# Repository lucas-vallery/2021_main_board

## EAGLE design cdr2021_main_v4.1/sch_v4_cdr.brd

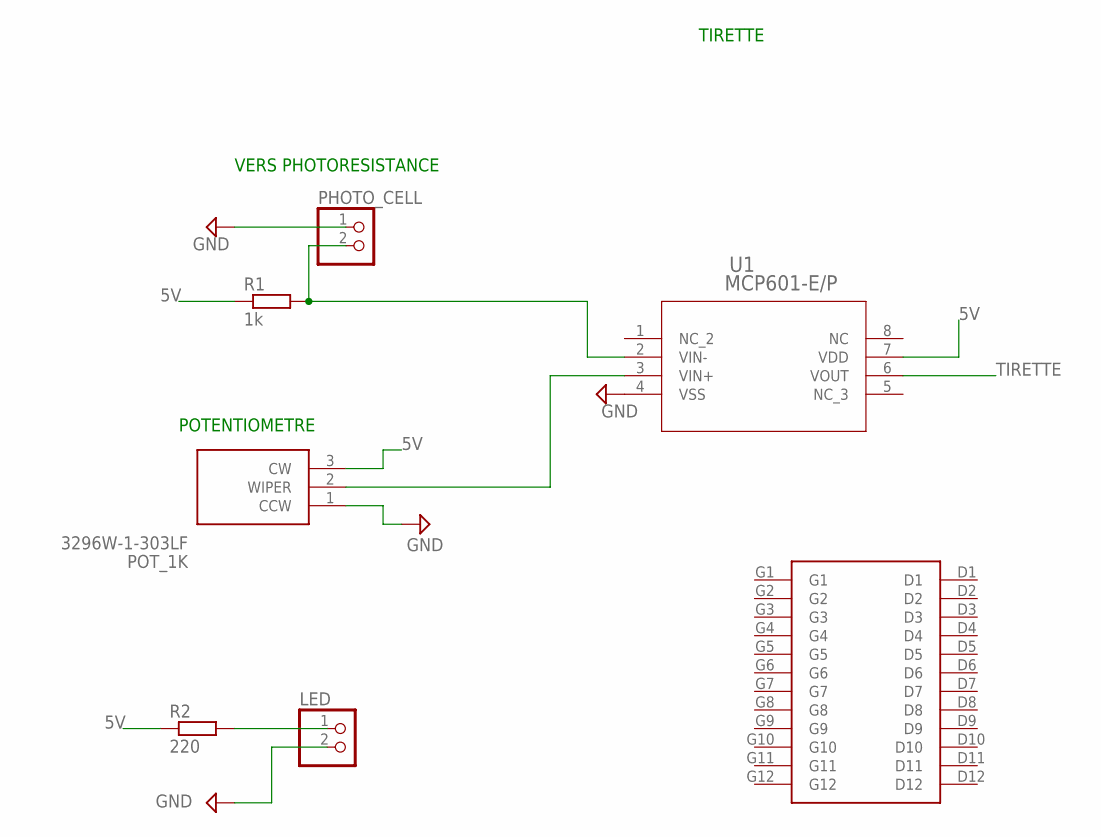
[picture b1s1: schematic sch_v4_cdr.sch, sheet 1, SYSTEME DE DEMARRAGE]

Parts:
LED: PINHD-1X2; 1X02
PHOTO_CELL: PINHD-1X2; 1X02
POT_1K: 3296W-1-303LF; 3296W-1
R1: 1k; 0204/7
R2: 220; 0204/7
U1: MCP601-E/P; PDIP8_300MC_MCH
U$5: MATRIX_12X12

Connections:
5V: POT_1K.3 (CW), R1.1, R2.1, U1.7 (VDD); also elsewhere on the board
GND: LED.2, PHOTO_CELL.1, POT_1K.1 (CCW), U1.4 (VSS); also elsewhere on the board
unnamed: PHOTO_CELL.2, R1.2, U1.2 (VIN-)
unnamed: POT_1K.2 (WIPER), U1.3 (VIN+)
unnamed: LED.1, R2.2
TIRETTE: U1.6 (VOUT); also elsewhere on the board

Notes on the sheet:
VERS PHOTORESISTANCE
POTENTIOMETRE
TIRETTE

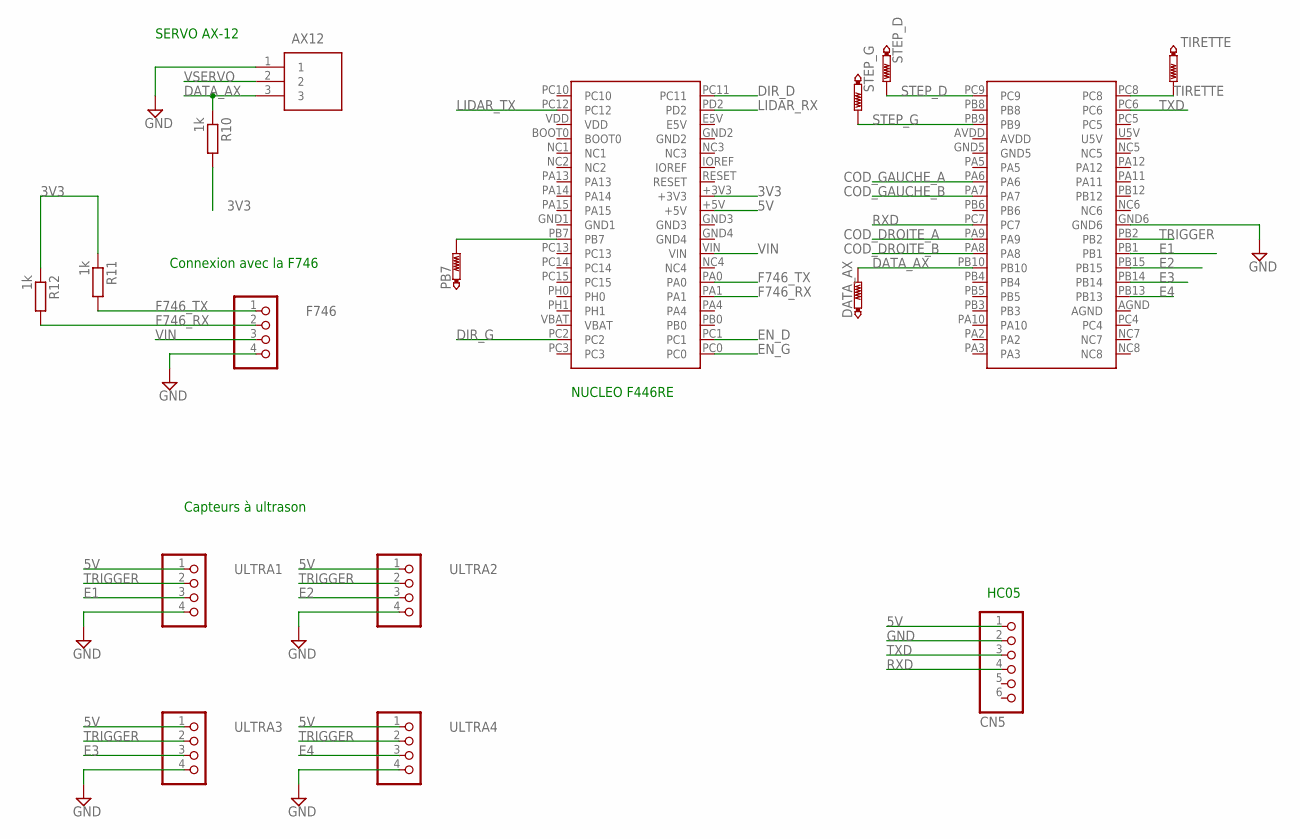
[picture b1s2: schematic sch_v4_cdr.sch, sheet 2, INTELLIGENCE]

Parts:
AX12: 22-03-5035; SHDR3W60P0X250_1X3_990X490X590
DATA_AX: PTR1PAD1-13; P1-13
F746: PINHD-1X4; 1X04
JP4: CN5; 1X06
PB7: PTR1PAD1-13; P1-13
R10, R11, R12: 1k; 0204/7
STEP_D: PTR1PAD1-13; P1-13
STEP_G: PTR1PAD1-13; P1-13
TIRETTE: PTR1PAD1-13; P1-13
U$1: NUCLEO_F446RE; MB1136
ULTRA1, ULTRA2, ULTRA3, ULTRA4: PINHD-1X4; 1X04

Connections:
3V3: R10.2, R11.1, R12.1, U$1.+3V3
5V: JP4.1, U$1.+5V, ULTRA1.1, ULTRA2.1, ULTRA3.1, ULTRA4.1; also elsewhere on the board
COD_DROITE_A: U$1.PA9; also elsewhere on the board
COD_DROITE_B: U$1.PA8; also elsewhere on the board
COD_GAUCHE_A: U$1.PA6; also elsewhere on the board
COD_GAUCHE_B: U$1.PA7; also elsewhere on the board
DATA_AX: AX12.3, DATA_AX.TP, R10.1, U$1.PB10
DIR_D: U$1.PC11; also elsewhere on the board
DIR_G: U$1.PC2; also elsewhere on the board
E1: U$1.PB1, ULTRA1.3
E2: U$1.PB15, ULTRA2.3
E3: U$1.PB14, ULTRA3.3
E4: U$1.PB13, ULTRA4.3
EN_D: U$1.PC1; also elsewhere on the board
EN_G: U$1.PC0; also elsewhere on the board
F746_RX: F746.2, R12.2, U$1.PA1
F746_TX: F746.1, R11.2, U$1.PA0
GND: AX12.1, F746.4, JP4.2, U$1.GND6, ULTRA1.4, ULTRA2.4, ULTRA3.4, ULTRA4.4; also elsewhere on the board
LIDAR_RX: U$1.PD2; also elsewhere on the board
LIDAR_TX: U$1.PC12; also elsewhere on the board
unnamed: PB7.TP, U$1.PB7
RXD: JP4.4, U$1.PC7
STEP_D: STEP_D.TP, U$1.PC9; also elsewhere on the board
STEP_G: STEP_G.TP, U$1.PB9; also elsewhere on the board
TIRETTE: TIRETTE.TP, U$1.PC8; also elsewhere on the board
TRIGGER: U$1.PB2, ULTRA1.2, ULTRA2.2, ULTRA3.2, ULTRA4.2
TXD: JP4.3, U$1.PC6
VIN: F746.3, U$1.VIN; also elsewhere on the board
VSERVO: AX12.2; also elsewhere on the board

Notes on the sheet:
NUCLEO F446RE
Connexion avec la F746
SERVO AX-12
Capteurs à ultrason
HC05

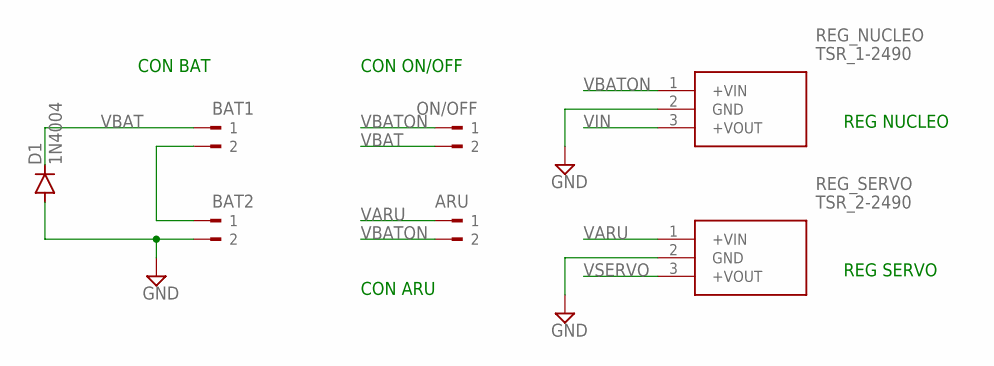
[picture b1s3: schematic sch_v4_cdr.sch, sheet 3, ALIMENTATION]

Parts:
ARU: 180G-2
BAT1, BAT2: 180G-2
D1: 1N4004; DO41-10
ON/OFF: 180G-2
REG_NUCLEO: TSR_1-2490; TSR_1-24XX
REG_SERVO: TSR_2-2490; TSR_2-24XX

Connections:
GND: BAT2.2, D1.A, REG_NUCLEO.2 (GND), REG_SERVO.2 (GND); also elsewhere on the board
unnamed: BAT1.2, BAT2.1
VARU: ARU.1, REG_SERVO.1 (+VIN); also elsewhere on the board
VBAT: BAT1.1, D1.C, ON/OFF.2
VBATON: ARU.2, ON/OFF.1, REG_NUCLEO.1 (+VIN)
VIN: REG_NUCLEO.3 (+VOUT); also elsewhere on the board
VSERVO: REG_SERVO.3 (+VOUT); also elsewhere on the board

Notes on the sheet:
CON BAT
CON ON/OFF
CON ARU
REG NUCLEO
REG SERVO

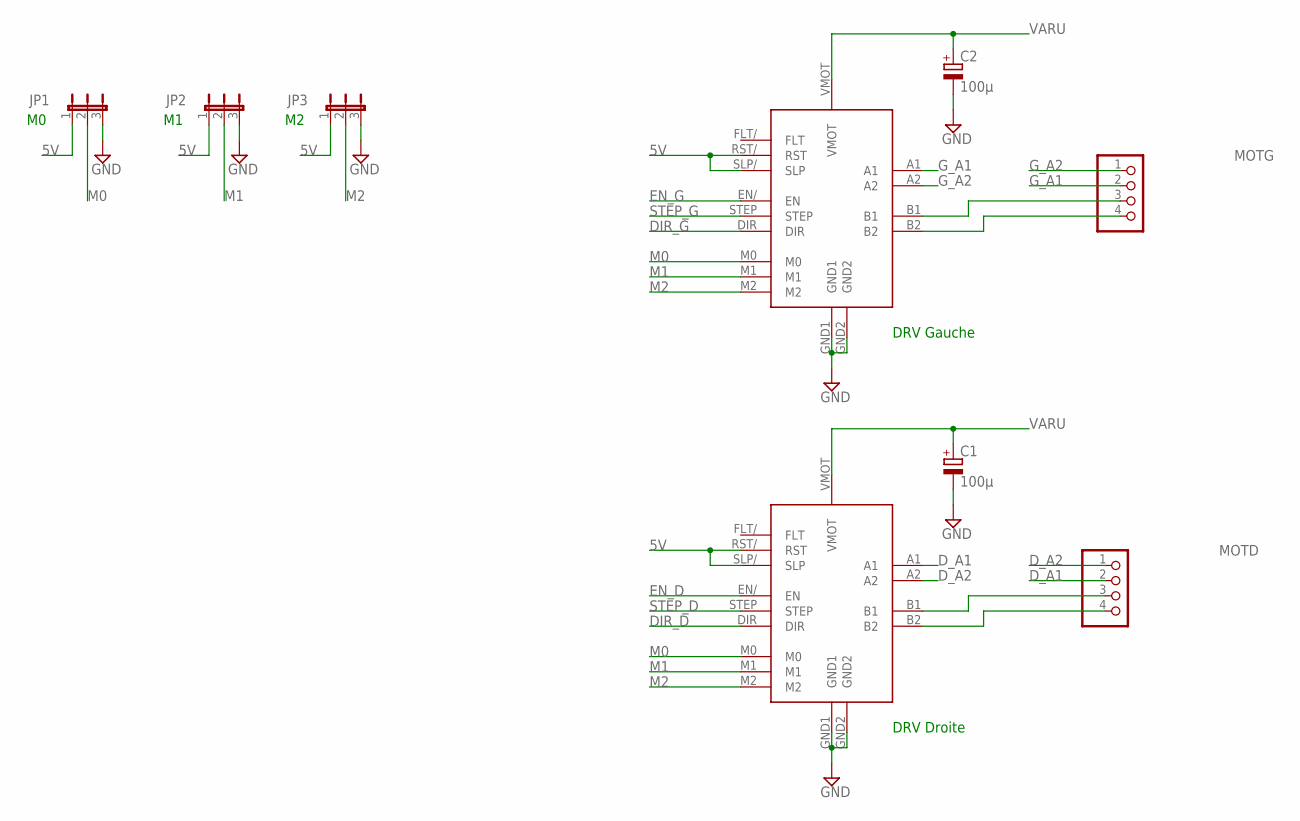
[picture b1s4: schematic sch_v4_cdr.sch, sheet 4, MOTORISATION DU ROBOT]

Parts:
C1, C2: 100µ; SANYO-OSCON_A
JP1, JP2, JP3: JP2E; JP2
MOTD: PINHD-1X4; 1X04
MOTG: PINHD-1X4; 1X04
U$2, U$3: POLOLU_DRV8825

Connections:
5V: JP1.1, JP2.1, JP3.1, U$2.RST/ (RST), U$2.SLP/ (SLP), U$3.RST/ (RST), U$3.SLP/ (SLP); also elsewhere on the board
DIR_D: U$3.DIR; also elsewhere on the board
DIR_G: U$2.DIR; also elsewhere on the board
D_A1: MOTD.2, U$3.A1
D_A2: MOTD.1, U$3.A2
EN_D: U$3.EN/ (EN); also elsewhere on the board
EN_G: U$2.EN/ (EN); also elsewhere on the board
GND: C1.-, C2.-, JP1.3, JP2.3, JP3.3, U$2.GND1, U$2.GND2, U$3.GND1, U$3.GND2; also elsewhere on the board
G_A1: MOTG.2, U$2.A1
G_A2: MOTG.1, U$2.A2
M0: JP1.2, U$2.M0, U$3.M0
M1: JP2.2, U$2.M1, U$3.M1
M2: JP3.2, U$2.M2, U$3.M2
unnamed: MOTG.3, U$2.B1
unnamed: MOTG.4, U$2.B2
unnamed: MOTD.3, U$3.B1
unnamed: MOTD.4, U$3.B2
STEP_D: U$3.STEP; also elsewhere on the board
STEP_G: U$2.STEP; also elsewhere on the board
VARU: C1.+, C2.+, U$2.VMOT, U$3.VMOT; also elsewhere on the board

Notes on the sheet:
DRV Gauche
DRV Droite

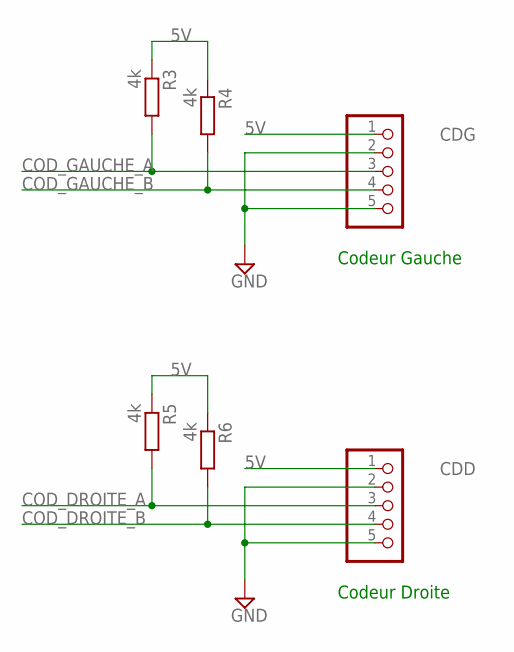
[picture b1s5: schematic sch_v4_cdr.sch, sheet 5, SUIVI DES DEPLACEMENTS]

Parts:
CDD: PINHD-1X5; 1X05
CDG: PINHD-1X5; 1X05
R3, R4, R5, R6: 4k; 0204/7

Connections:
5V: CDD.1, CDG.1, R3.1, R4.1, R5.1, R6.1; also elsewhere on the board
COD_DROITE_A: CDD.3, R5.2; also elsewhere on the board
COD_DROITE_B: CDD.4, R6.2; also elsewhere on the board
COD_GAUCHE_A: CDG.3, R3.2; also elsewhere on the board
COD_GAUCHE_B: CDG.4, R4.2; also elsewhere on the board
GND: CDD.2, CDD.5, CDG.2, CDG.5; also elsewhere on the board

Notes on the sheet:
Codeur Gauche
Codeur Droite

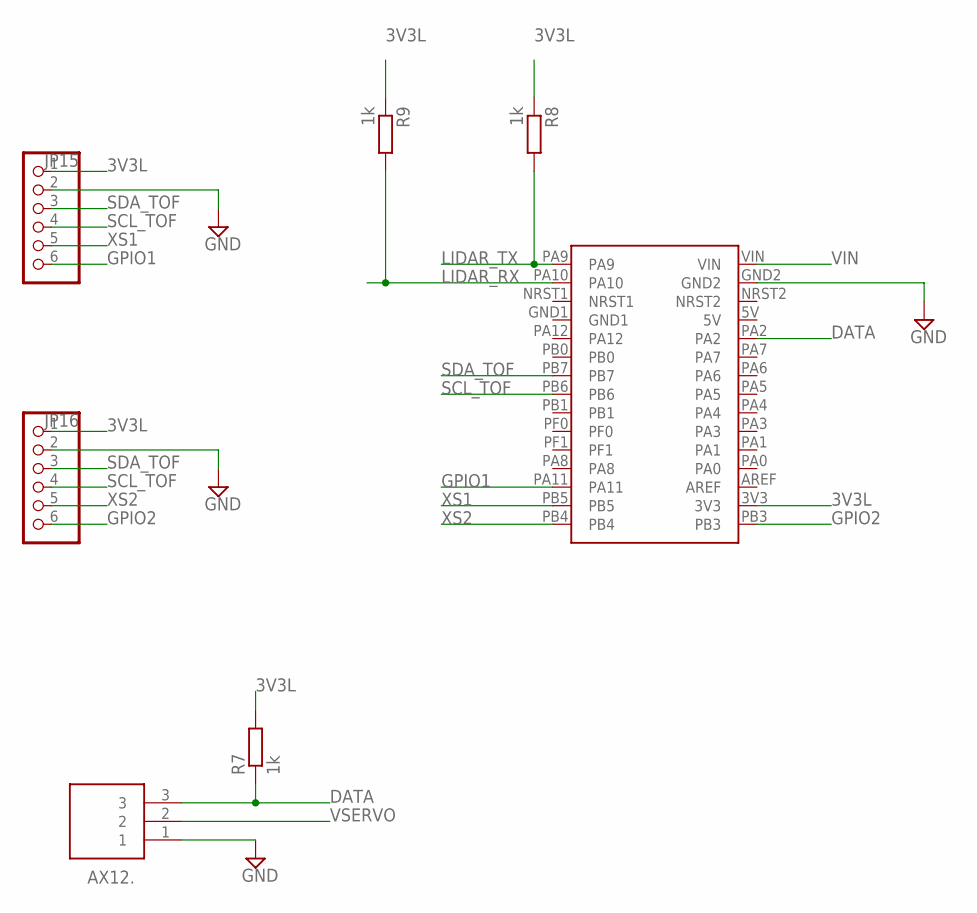
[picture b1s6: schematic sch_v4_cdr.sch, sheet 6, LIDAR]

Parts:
AX12.: 22-03-5035; SHDR3W60P0X250_1X3_990X490X590
JP15, JP16: PINHD-1X6; 1X06
R7, R8, R9: 1k; 0204/7
U$4: NUCLEO_F303K8; MB1180

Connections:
3V3L: JP15.1, JP16.1, R7.2, R8.1, R9.1, U$4.3V3
DATA: AX12..3, R7.1, U$4.PA2
GND: AX12..1, JP15.2, JP16.2, U$4.GND2; also elsewhere on the board
GPIO1: JP15.6, U$4.PA11
GPIO2: JP16.6, U$4.PB3
LIDAR_RX: R9.2, U$4.PA10; also elsewhere on the board
LIDAR_TX: R8.2, U$4.PA9; also elsewhere on the board
SCL_TOF: JP15.4, JP16.4, U$4.PB6
SDA_TOF: JP15.3, JP16.3, U$4.PB7
VIN: U$4.VIN; also elsewhere on the board
VSERVO: AX12..2; also elsewhere on the board
XS1: JP15.5, U$4.PB5
XS2: JP16.5, U$4.PB4

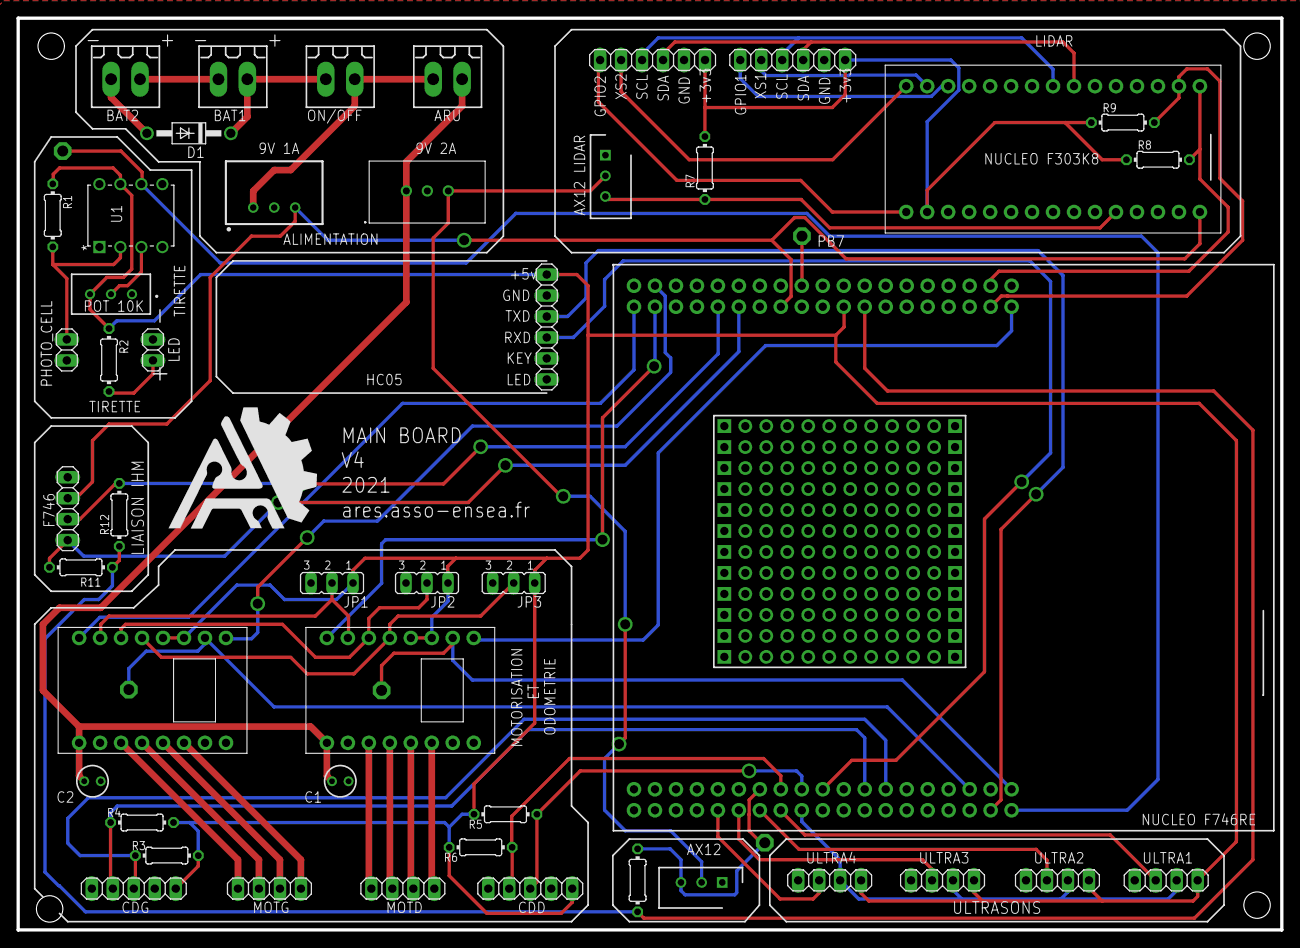
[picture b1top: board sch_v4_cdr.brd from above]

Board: 2 copper layers, 153.0 x 110.4 mm, 52 parts (0 on the bottom side), 55 nets.

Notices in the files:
parts and their libraries:
COPYRIGHT: Copyright (C) 2018 Accelerated Designs. All rights reserved
